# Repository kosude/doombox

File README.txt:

This repository contains all documentation and code for the DOOMbox Project.

My final goal for this project is an encased physical console, based on the
Pico 2 (RP2350 using Arm) dedicated to running a purpose-built DOOM clone,
maybe with a bunch of extra features thrown in for fun.

This is an evolution of my previous ambition to write a functional DOOM clone
in pure x86 assembly. The software for DOOMbox will instead be written in a
combination of C and assembly. The old project is below:

    https://gitlab.com/kosude/doom

It should be noted that Graham Saunderson has done something similar:

    https://kilograham.github.io/rp2040-doom

To be clear, DOOMbox was not inspired by RP2040 Doom, though his documentation
will probably be very helpful going forward, as I will be using similar
hardware. The main difference is that this project is more intended to just be
a fun learning experience as opposed to trying to make an authentic DOOM port
(which is why I'm not porting at all).

-------------------------[ BUILDING DOOMBOX FIRMWARE ]-------------------------

Building the firmware requires CMake, as well as the pico-sdk:

    https://github.com/raspberrypi/pico-sdk

Then (in the root project directory) configure for the desired build type:
    $ cmake . -Bbuild -DCMAKE_BUILD_TYPE=(Debug|Release)
and build:
    $ cmake --build build

Using the Debug build type enables stdio logging, which can help in debugging
(see the relevant section below).

Make sure the DBX_BUILD_FIRMWARE build option is set to ON - this is the
default value.

------------------------[ DEBUGGING DOOMBOX FIRMWARE ]-------------------------

Raspberry Pi document how to debug Pico software in one of their manuals:

    https://datasheets.raspberrypi.com/pico/getting-started-with-pico.pdf

There are multiple ways to debug, but the only properly tested route for
DOOMbox is with a second Pico, since it's the best way IMO and I don't want to
buy a "debug probe".

To go that route, GDB is required as well as Raspberry Pi's OpenOCD fork:

    https://github.com/raspberrypi/openocd

Program and set up the second Pico as shown in the Getting Started guide above
(I use the official debugprobe firmware) and then connect it to the host via
USB.

The rest of the process can be done for you by the Unified Programming and
Debugging Utility (updu.sh) in the scripts/ directory, which will by default
open a GDB session for debugging.

Reading stdout can be done in any standard way. For instance, using minicom
with a second Pico, run:

    $ minicom -b 115200 -o -D /dev/ttyACM0

(of course the device might be different)

###############################################################################

The rest of this document serves as the project's most current design
specification. Kicad schematics are also provided in the hardware/ directory.

-------------------------------[ PREREQUISITES ]-------------------------------

    ==== UNITS ====

The design specification will follow IEC 80000-13 (B: byte, b: bit):
    * 1 B   = 8 b
    * 1 kiB = 1024 B
    * 1 kB  = 1000 B
    * etc...
In all cases, use of the standard SI units indicates a decimal value, whereas
use of the IEC 80000-13 units indicates a binary value.

-----------------------------[ FILESYSTEM LAYOUT ]-----------------------------

Available capacity:
    * 4 MiB on-board flash/NVM

--------------------------------[ MEMORY MAP ]---------------------------------

TO-DO: specify memory map after reserved quantities are designated

Available memory:
    * 512 kiB on-chip SRAM
    * 2 x 4 kiB banks

Reserved memory quantities:
    * 128 kB for VGA output (320x200, 8 bpp):
        64 kB front buffer
        64 kB back buffer

----------------------------[ POWER SPECIFICATION ]----------------------------

For the time being, a simple LDO regulator is being used to step down input
voltage to 5V.

---------------------------[ GRAPHICS SPECIFICATION ]--------------------------

DOOMbox provides graphical output via VGA. Colour data is output in parallel
from the Pico directly to the VGA connector.

Colour data is output in the form RGB-332, i.e. 3 bits for the red and green
channels, and 2 for the blue.

On the Pico, GPIOs 2-9 are reserved for video data and and 10-11 for HSync and
VSync signals respectively.

When writing colour data serially, the bit-order is as follows:
    B1 B0 G2 G1 G0 R2 R1 R0
  first ---------------> last
where the leftmost bit of each channel is the MSB as usual.

Time-critical PIO machines are used for producing the synchronisation signals.
For detailed VGA timing information, see the TIMINGS.txt file in the
firmware/kernel/drivers/vga/ directory.

----------------------------[ AUDIO SPECIFICATION ]----------------------------

Stereo audio is provided via pulse width modulation (PWM). GPIOs 8 and 9 are
reserved for this purpose, where GPIO8 outputs left audio, and GPIO9 right.

    TODO better description

----------------------------[ INPUT SPECIFICATION ]----------------------------

    TODO

Required controls:
    * Move forward + move backwards | Single joystick: vertical: moving
    * Turn left + turn right        |                  horizontal: turning
    * Strafe                          Modifier btn: strafe with hoz. joystick
    * Run / speed modifier            Modifier button
    * Fire                            Button
    * Interact                        Button
    * Menu                            Button
    * Weapon selection                7 buttons

Automap necessary?

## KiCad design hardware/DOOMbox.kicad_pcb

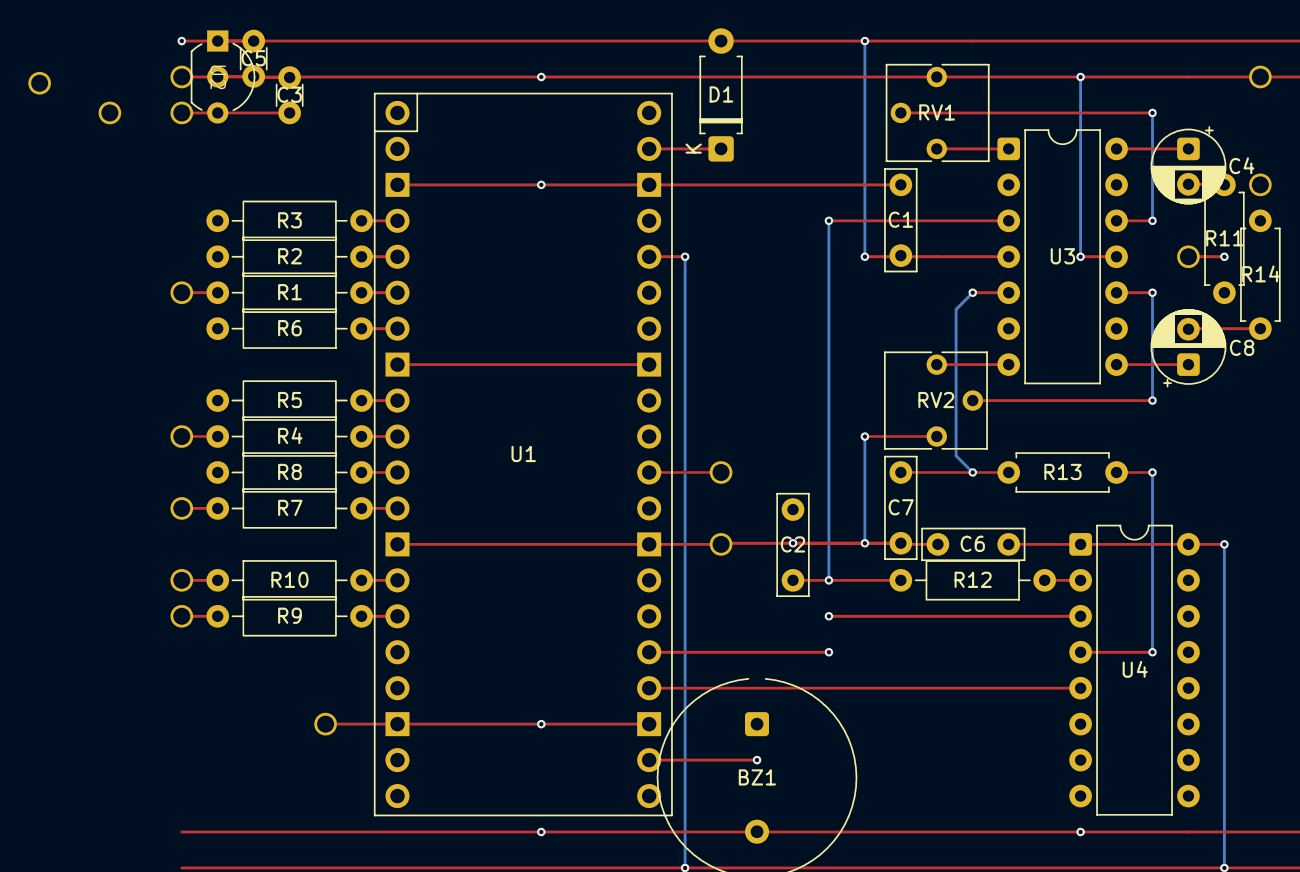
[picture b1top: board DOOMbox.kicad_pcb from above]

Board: 4 copper layers, 43 parts (0 on the bottom side), 38 nets.

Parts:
BZ1: Buzzer; Indicator_PUI_AI-1440-TWT-24V-2-R
C1, C6: 100n; C_Rect_L7.0mm_W2.0mm_P5.00mm
C2, C7: 8n2; C_Rect_L7.0mm_W2.0mm_P5.00mm
C3: 1u; C_Disc_D3.0mm_W1.6mm_P2.50mm
C4, C8: 4u7; CP_Radial_D5.0mm_P2.50mm
C5: 2u2; C_Disc_D3.0mm_W1.6mm_P2.50mm
D1: D; D_A-405_P7.62mm_Horizontal
J1, J1#2, J1#3, J1#4, J1#5, J1#6: DE15_Socket_HighDensity; Peripheral_Offboard
J2, J2#2, J2#3: AudioJack3; Peripheral_Offboard
R1, R4: 499R; R_Axial_DIN0207_L6.3mm_D2.5mm_P10.16mm_Horizontal
R2, R5: 1K; R_Axial_DIN0207_L6.3mm_D2.5mm_P10.16mm_Horizontal
R3, R6: 2K; R_Axial_DIN0207_L6.3mm_D2.5mm_P10.16mm_Horizontal
R7: 412R; R_Axial_DIN0207_L6.3mm_D2.5mm_P10.16mm_Horizontal
R8, R12: 826R; R_Axial_DIN0207_L6.3mm_D2.5mm_P10.16mm_Horizontal
R9, R10: 47R; R_Axial_DIN0207_L6.3mm_D2.5mm_P10.16mm_Horizontal
R11, R14: 10K; R_Axial_DIN0207_L6.3mm_D2.5mm_P7.62mm_Horizontal
R13: 826R; R_Axial_DIN0207_L6.3mm_D2.5mm_P7.62mm_Horizontal
RV1, RV2: 100K; Potentiometer_Vishay_T73YP_Vertical
SW1, SW1#2, SW1#3: SW_SPST; Peripheral_Offboard
SW2: SW_Push; Peripheral_Offboard
U1: RPi Pico 2; RPi_Pico_SMD_TH
U2: AP7381-50SA-7; AP7381-TO92
U3: LM324N; DIP-14_W7.62mm
U4: CD4010BE; DIP-16_W7.62mm

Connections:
+3V3: C6.1, U1.36 (3V3), U4.1 (VCC), U4.16 (VDD)
+5V: C1.1, C5.1, D1.2 (A), U2.1 (VI), U3.4 (V+)
GND: BZ1.2 (-), C1.2, C2.2, C3.2, C5.2, C6.2, C7.2, J1#6.VGAGND, J2#2.S, RV1.1, RV2.1, U1.3 (GND), U1.8 (GND), U1.13 (GND), U1.18 (GND), U1.23 (GND), U1.28 (GND), U1.33 (AGND), U1.38 (GND), U2.2 (VO), U3.11 (V-), U4.8 (VSS)
HSYNC: R10.2, U1.14 (GPIO10)
unnamed: BZ1.1 (+), U1.22 (GPIO17)
unnamed: C4.2, R11.1
unnamed: C8.2, R14.1
unnamed: D1.1 (K), U1.39 (VSYS)
unnamed: J1#3.VGA1, R1.2, R2.2, R3.2
unnamed: J1#5.VGA2, R4.2, R5.2, R6.2
unnamed: J1.VGA3, R7.2, R8.2
unnamed: J1#4.VGA13, R10.1
unnamed: J1#2.VGA14, R9.1
unnamed: J2#3.R, R14.2
unnamed: J2.T, R11.2
unnamed: C3.1, SW1.1 (A), SW1#3.1 (A), U2.3 (GND)
unnamed: SW2.1, U1.30 (RUN)
unnamed: C2.1, R12.2, U3.3 (+)
unnamed: RV1.3, U3.1, U3.2 (-)
unnamed: C7.1, R13.2, U3.5 (+)
unnamed: RV2.3, U3.6 (-), U3.7
unnamed: RV2.2, U3.10 (+)
unnamed: C8.1, U3.8, U3.9 (-)
unnamed: RV1.2, U3.12 (+)
unnamed: C4.1, U3.13 (-), U3.14
unnamed: R12.1, U4.2 (G)
unnamed: R13.1, U4.4 (H)
PWM_AUL: U1.25 (GPIO19), U4.3 (A)
PWM_AUR: U1.24 (GPIO18), U4.5 (B)
VGA_B0: R8.1, U1.11 (GPIO8)
VGA_B1: R7.1, U1.12 (GPIO9)
VGA_G0: R6.1, U1.7 (GPIO5)
VGA_G1: R5.1, U1.9 (GPIO6)
VGA_G2: R4.1, U1.10 (GPIO7)
VGA_R0: R3.1, U1.4 (GPIO2)
VGA_R1: R2.1, U1.5 (GPIO3)
VGA_R2: R1.1, U1.6 (GPIO4)
VSYNC: R9.2, U1.15 (GPIO11)

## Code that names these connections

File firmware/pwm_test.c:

/*
 * Copyright (c) 2025 Jack Bennett.
 * All Rights Reserved.
 *
 * See the LICENCE file for more information.
 */

#include <hardware/clocks.h>
#include <hardware/pwm.h>
#include <hardware/sync.h>
#include <pico/stdlib.h>

// GPIO pin for the onboard speaker
#define GPIO_OBSPKR 22

// GPIO pins for left and right PWM audio, respectively
#define GPIO_PWM_AUL 8
#define GPIO_PWM_AUR 9

// see 12.5.2: https://datasheets.raspberrypi.com/rp2350/rp2350-datasheet.pdf
#define SLICE_AUX 4 // GPIO8 and GPIO9
#define CHAN_AUL  0 // GPIO8
#define CHAN_AUR  1 // GPIO9

#include "pwm_samples.h"
static int cursor = 0;

// PWM interrupt handler which advances the sample cursor.
// Bit-shifting by 3 means each sample is played for 8 cycles
void
pwm_isr()
{
    pwm_clear_irq(SLICE_AUX);

    if (cursor < (samplen << 3) - 1) {
        // not doing stereo stuff yet
        pwm_set_chan_level(SLICE_AUX, CHAN_AUL, samples[cursor >> 3]);
        pwm_set_chan_level(SLICE_AUX, CHAN_AUR, samples[cursor >> 3]);
        cursor++;
    } else {
        // reset to start
        cursor = 0;
    }
}

int
main(void)
{
    // GPIO init
    gpio_init(PICO_DEFAULT_LED_PIN);
    gpio_init(GPIO_OBSPKR);
    gpio_set_dir(PICO_DEFAULT_LED_PIN, GPIO_OUT);
    gpio_set_dir(GPIO_OBSPKR, GPIO_OUT);

    // turn on onboard LED
    gpio_put(PICO_DEFAULT_LED_PIN, 1);
    gpio_put(PICO_DEFAULT_LED_PIN, 0);
    gpio_put(PICO_DEFAULT_LED_PIN, 1);

    // TODO optionally beep onboard speaker on startup
    // gpio_put(GPIO_OBSPKR, 1);
    // sleep_ms(100);
    // gpio_put(GPIO_OBSPKR, 0);

    gpio_set_function(GPIO_PWM_AUL, GPIO_FUNC_PWM);
    gpio_set_function(GPIO_PWM_AUR, GPIO_FUNC_PWM);

    pwm_config cfg = pwm_get_default_config();

    // ------------------------------------------------------------------------

    // e.g. for outputting a C note
    // ref https://datasheets.raspberrypi.com/rp2350/rp2350-datasheet.pdf
    //     sect 12.5.2.6: configuring PWM period
    // ----------------------------
    // target freq = 523.25 Hz
    // and system freq assumed to be 150 MHz (correct?)
    // therefore target period = ~286670 clk cycles per PWM cycle
    // so...
    // with DIV = 256 (max)
    //      CSR_PH_CORRECT = 0 (i.e. not phase-correct mode)
    // working back from formula given in the datasheet:
    //      TOP = ~ 1119

    pwm_config_set_clkdiv_mode(&cfg, PWM_DIV_FREE_RUNNING);
    pwm_config_set_phase_correct(&cfg, 0);
    pwm_config_set_clkdiv_int_frac(&cfg, 0, 0);
    pwm_config_set_wrap(&cfg, 1119);

    pwm_init(SLICE_AUX, &cfg, true);

    pwm_set_chan_level(SLICE_AUX, CHAN_AUL, 100);
    pwm_set_chan_level(SLICE_AUX, CHAN_AUR, 100);

    // ------------------------------------------------------------------------

    // // Playing WAV audio test
    // // ----------------------------
    // // system freq 150 MHz (correct?)
    // // with TOP = 213
    // //      CSR_PH_CORRECT = 0
    // // playing each sample for 8 cycles, so for a sample rate of...
    // //      11kHz --> DIV = 8.0
    // //      22kHz --> DIV = 4.0, etc.

    // // setup interrupt handler
    // pwm_clear_irq(SLICE_AUX);
    // pwm_set_irq_enabled(SLICE_AUX, 1);
    // irq_set_exclusive_handler(PWM_IRQ_WRAP, pwm_isr);
    // irq_set_enabled(PWM_IRQ_WRAP, 1);

    // pwm_config_set_clkdiv_mode(&cfg, PWM_DIV_FREE_RUNNING);
    // pwm_config_set_phase_correct(&cfg, 0);
    // pwm_config_set_clkdiv(&cfg, 8.0);
    // pwm_config_set_wrap(&cfg, 213);

    // pwm_init(SLICE_AUX, &cfg, true);

    // // hold for interrupts
    // for (;;) {
    //     __wfi(); // ARM instruction
    // }

    // ------------------------------------------------------------------------
}

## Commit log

2025-05-21 Update readme a bit
2025-05-22 Kicad project init
2025-05-23 Track necessary KiCad libraries + symbols
2025-05-25 Schematic: add resistor ladder DACs for video data output
2025-07-22 Add component sheet + VGA output note in schematic
2025-07-22 Finalise VGA output schematic now w/ MCP23S08 SPI expander
2025-07-22 More schematic changes
2025-07-23 Document inputs and storage info, and add PWM audio schematic
2025-07-24 Schem for power circuit + rpi SWD pins and reset button
2025-07-24 Clean up symbols and add footprint for MCP23S08
2025-07-24 Rename parts sheet to bom.ods
2025-07-25 Add design for audio output w/ quad opamp + reorganise schematic
2025-07-25 Remove BOM sheet
2025-07-28 Remove outdated to-order list
2025-07-28 README update
2025-08-01 Rename kicad directory -> hardware/
2025-08-01 Set up CMake project for firmware (linked to pico-sdk)
2025-08-01 Restructure CMake project and document build process in README
2025-08-01 Add .clang-format config
2025-08-01 Temp main.c cleanup
2025-08-01 Add MIT licence
2025-08-06 Add blink example code to main.c for testing
2025-08-06 Add firmware_ocd.sh and gdbinit for debugging via second pico
2025-08-08 Some PWM programming and testing to play a C note
2025-08-08 Some PWM notes added to schematic
2025-08-08 Add GPIO for onboard speaker to current test .c src
2025-08-09 Add support for flashing+debugging in one call to firmware_ocd.sh
2025-08-09 Remove -s option from firmware_ocd.sh util script
2025-08-09 Rename firmware_ocd.sh to updu.sh and gdbinit to updu_gdbinit
2025-08-09 UPDU: add -d and -K options
2025-08-09 More openocd scripting stuff
2025-08-12 Major utility script refactor, add ocdsrv.sh for centralised management
2025-08-12 Some more small script changes
2025-08-12 Actual start made on the firmware codebase
2025-08-12 Move firmware code into kernel/ subdir, add kpanic function
2025-08-15 Add starting point of the driver for the onboard buzzer
2025-08-15 Start work on the VGA driver
2025-08-15 Add very thin macro wrapper around stdio funcs
2025-08-15 SPI testing for VGA (+ fix MCP address pins not tied to GND)
2025-08-20 Working VGA output direct from Pico (ie. removed MCP23S08) + palette
2025-08-20 Clean-up, removed unused/working comments and todo's
2025-08-22 Create VRAM static video memory buffer, organise VGA driver code
2025-08-23 Adjust VGA timings for 320x400 output (will draw each line twice)
2025-08-23 Add bitmap font for VGA text rendering + putc function
2025-08-23 Add VGA text functions for manipulating the put head
2025-08-23 Add vga_puts function
2025-08-23 Update README.txt: remove mention of now-unused SPI for video
2025-08-23 Unnecessary include clean-up
2025-08-23 Move video palette test function into new stress.h
2025-08-23 Add vga_stress_grid() for seeing timing instabilities
2025-08-23 Rename __vgafont => __vga_font (tidy conventions)
    The vram component of the vga driver still gets its own prefix
    because typing VRAM instead of VGA_VRAM is nice
2025-08-23 Move vga driver .pio files into their own directory
2025-08-25 Draw each line twice to fix duplicated framebuffer bug
2025-08-25 VGA driver: implement VRAM double buffering
2025-08-25 Implement async "onboard" piezo speaker driver
    (also remove some unused include directives)
2025-08-25 Remove old todo
2025-08-25 Add vga_stress_atlas() for testing font/text rendering
2025-08-25 Add game abstraction layer + game_main() entrypoint
2025-08-25 Change include directory for kernel symbols
2025-08-25 Set up game geometry data and implement line-drawing algorithm
2025-08-25 Maybe fix double-buffering issues?
2025-08-26 Pseudo-3D perspective rendering (correct but quite unoptimised)
2025-08-29 Stripboard layout WIP + custom footprints
2025-08-30 Complete stripboard design
    Squashed commit of the following:
    commit dbad1e7bdfb2dba54c7140f3a2191c6905e5781a
    Author: Jack Bennett <jackbennett0708@gmail.com>
    Date: Sat Aug 30 16:36:03 2025 +0100
    Complete
    commit 05059f46a42e6744a15d06e69ba94dfb8af3ae9c
2025-08-31 Rework stripboard design (+ edit sb symbols)
2025-08-31 Shorten R12 and R13 + add missing cut
2025-08-31 Organise stripboard layers + offboard SW1
2025-09-02 Fix incorrect pins on U2 and accidental stripboard cut in U4
2026-01-03 Change to onboard speaker startup behaviour
